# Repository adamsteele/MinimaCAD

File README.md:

Minima CAD
==========

Credit goes to Adrian over at http://yo4hhp.wordpress.com/ who did the original Eagle work and Ashhar Farhan over at http://www.phonestack.com/farhan/minima.html for the original Minima design.

There is a mailing list at http://www.freelists.org/archive/minima/recent for the Minima radio.

==========

What I've done is combine the two radio boards in to a single eagle brd/sch file and wrote up a BOM for DigiKey.
What I'd like to do is be able to run boards off at OSHPark, buy a bag of parts of DigiKey and have a radio.

What still needs done:

- [ ] Hole Drill Sizes. Adrian designed this for ease of home manufacture not for OSHPark so it will take some tweaks.
- [ ] Cleanup silkscreen. It's pretty clean already there's just a bit of overlap here and there.
- [ ] Cleanup part values for consistency
- [ ] Cleanup BOM. There are a few resistor/capacitor lines that could be combined.
- [ ] Verify BOM. I went through and generally picked the cheapest parts available. Many of these have fairly loose tolerances which might not work in a radio (I don't know).

==========

Quick Notes:
- These boards aren't ready yet for OSHPark so don't spend the money on it just yet.
- The BOM is reasonably complete but it is missing tuning inductors and a knob. Money could easily be saved by not buying SMA connectors and using a bit of coax. The LCD could also be bought elsewhere to save money.

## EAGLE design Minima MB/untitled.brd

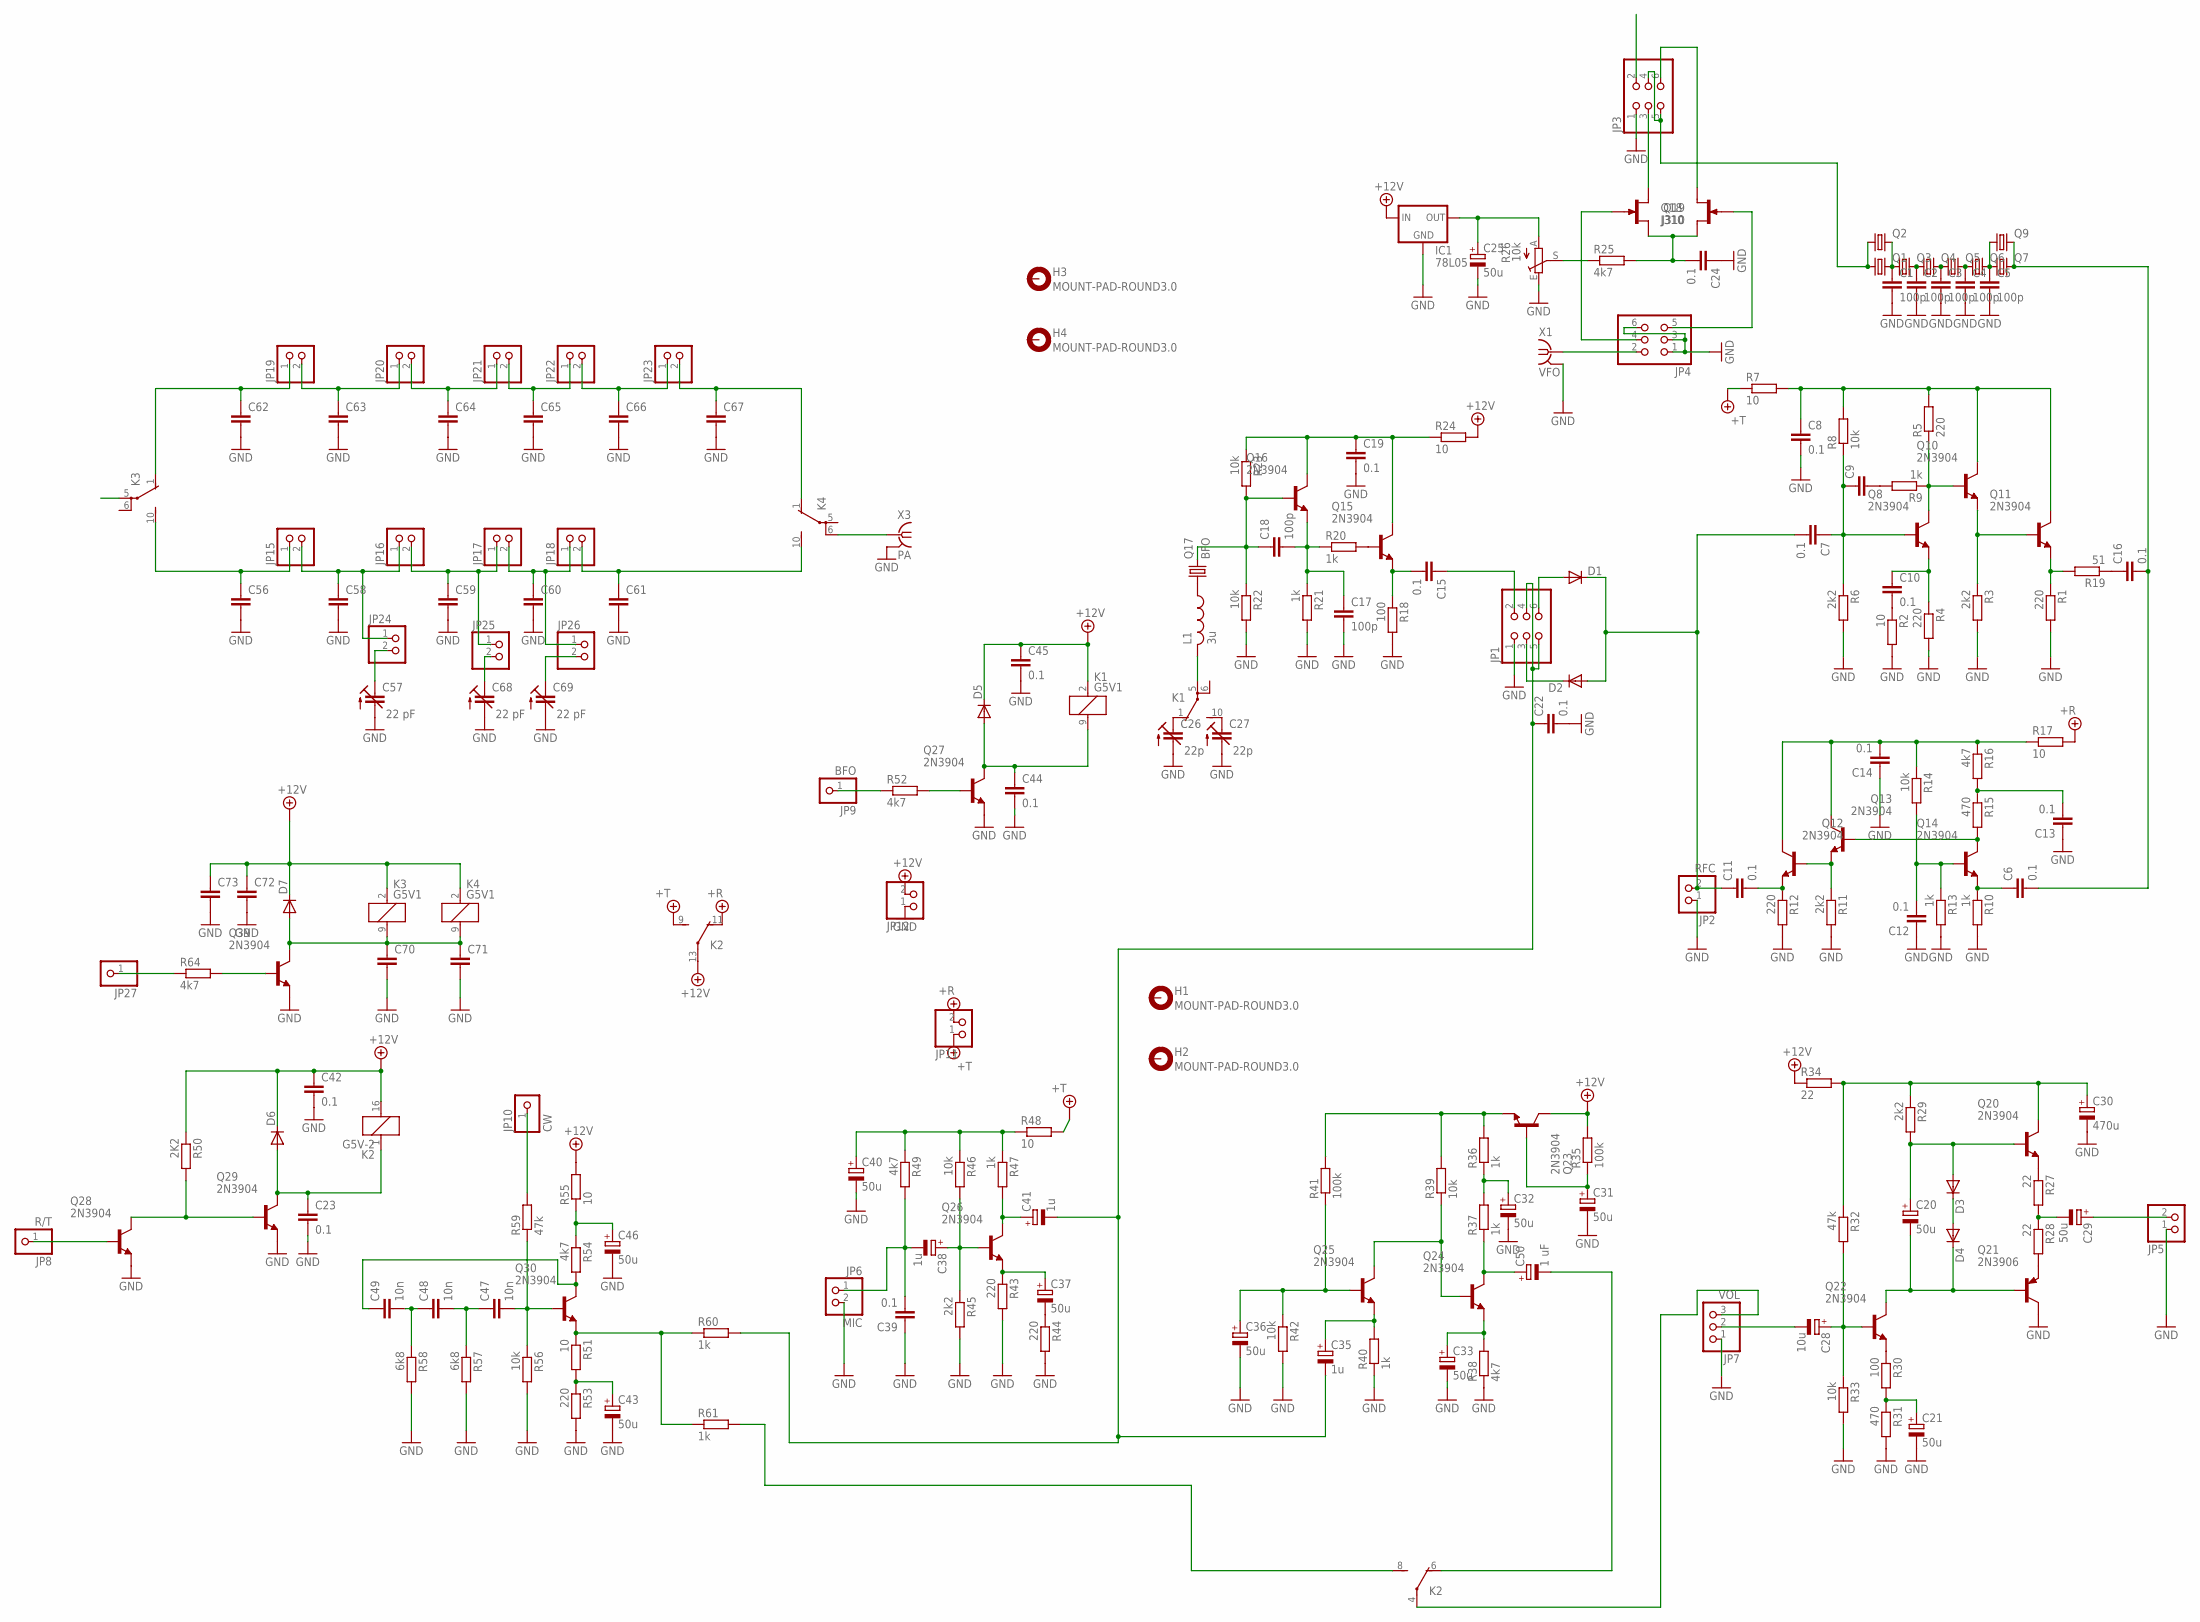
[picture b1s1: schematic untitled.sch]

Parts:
C1, C2, C3, C4, C5: 100p; C1206
C6, C7, C8, C10, C11, C12, C13, C14, C15, C16, C19, C22, C23, C24, C39, C42, C44, C45: 0.1; C050-024X044
C9, C56, C58, C59, C60, C61, C62, C63, C64, C65, C66, C67, C70, C71, C72, C73: C-EU050-024X044; C050-024X044
C17, C18: 100p; C050-024X044
C20, C21, C25, C29, C31, C32, C33, C36, C37, C40, C43, C46: 50u; E2,5-5
C26, C27: 22p; CTRIMTZ03
C28: 10u; E2,5-5
C30: 470u; E2,5-5
C35, C38, C41: 1u; E2,5-5
C47, C48, C49: 10n; C050-024X044
C50: 1 uF; E5-4
C57, C68, C69: 22 pF; CTRIMTZ03
D1, D2, D3, D4, D5, D6, D7: DIODE-D-5; D-5
H1, H2, H3, H4: MOUNT-PAD-ROUND3.0; 3,0-PAD
IC1: 78L05; 78LXX
JP1, JP3, JP4: PINHD-2X3; 2X03
JP2: RFC; 1X02
JP5, JP11, JP12, JP15, JP16, JP17, JP18, JP19, JP20, JP21, JP22, JP23, JP24, JP25, JP26: PINHD-1X2; 1X02
JP6: MIC; 1X02
JP7: VOL; 1X03
JP8: R/T; 1X01
JP9: BFO; 1X01
JP10: CW; 1X01
JP27: PINHD-1X1; 1X01
K1, K3, K4: G5V1
K2: G5V-2
L1: 3u; 0207/2V
Q1, Q2, Q3, Q4, Q5, Q6, Q7, Q9: CRYSTALHC49S; HC49/S
Q8, Q10, Q11, Q12, Q13, Q14, Q15, Q16, Q20, Q22, Q23, Q24, Q25, Q26, Q27, Q28, Q29, Q30, Q39: 2N3904; TO92
Q17: BFO; HC49/S
Q18, Q19: J310; TO92R
Q21: 2N3906; TO92
R1, R4, R5, R12, R43, R44, R53: 220; 0204/5
R2, R7, R17, R24, R48, R51, R55: 10; 0204/5
R3, R6, R11, R29, R45: 2k2; 0204/5
R8, R14, R22, R23, R33, R39, R42, R46, R56: 10k; 0204/5
R9, R10, R13, R20, R21, R36, R37, R40, R47, R60, R61: 1k; 0204/5
R15, R31: 470; 0204/5
R16, R25, R38, R49, R52, R54, R64: 4k7; 0204/5
R18, R30: 100; 0204/5
R19: 51; 0204/5
R26: 10k; CA6V
R27, R28, R34: 22; 0204/5
R32, R59: 47k; 0204/5
R35, R41: 100k; 0204/5
R50: 2K2; 0204/5
R57, R58: 6k8; 0204/5
X1: VFO; BU-SMA-V
X3: PA; BU-SMA-V

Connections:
+5V/1: JP11.2, K2.11 (O), R17.2
+5V/2: JP11.1, K2.9 (S), R7.1, R48.2
+12V: C42.1, C45.1, C72.1, C73.1, D5.C, D6.C, D7.C, IC1.IN, JP12.2, K1.2 (1), K2.13, K2.16 (2), K3.2 (1), K4.2 (1), Q23.1 (C), R24.2, R34.1, R35.2, R50.1, R55.2
GND: C1.2, C2.2, C3.2, C4.2, C5.2, C8.2, C12.1, C13.1, C14.1, C17.2, C19.2, C21.-, C22.2, C23.2, C24.1, C25.-, C26.2 (A), C27.2 (A), C30.-, C31.-, C32.-, C33.-, C36.-, C39.1, C40.-, C42.2, C43.-, C44.2, C45.2, C46.-, C56.2, C57.2 (A), C58.2, C59.2, C60.2, C61.2, C62.2, C63.2, C64.2, C65.2, C66.2, C67.2, C68.2 (A), C69.2 (A), C70.2, C71.2, C72.2, C73.2, IC1.GND, JP1.1, JP2.1, JP3.1, JP4.1, JP4.3, JP4.6, JP5.1, JP6.2, JP7.1, JP12.1, Q21.1 (C), Q27.3 (E), Q28.3 (E), Q29.3 (E), Q39.3 (E), R1.2, R2.2, R3.2, R4.2, R6.2, R10.2, R11.2, R12.2, R13.2, R18.2, R21.2, R22.2, R26.E, R31.2, R33.2, R38.1, R40.1, R42.2, R43.2, R44.2, R45.2, R53.2, R56.2, R57.2, R58.2, X1.2 (GND), X1.3 (GND), X1.4 (GND), X1.5 (GND), X3.2 (GND), X3.3 (GND), X3.4 (GND), X3.5 (GND)
unnamed: C1.1, Q1.2, Q2.2, Q3.1
unnamed: C2.1, Q3.2, Q4.1
unnamed: C3.1, Q4.2, Q5.1
unnamed: C4.1, Q5.2, Q6.1
unnamed: C5.1, Q6.2, Q7.1, Q9.1
unnamed: C6.2, C16.2, Q7.2, Q9.2
unnamed: C26.1 (E), K1.1 (O)
unnamed: C10.1, Q8.3 (E), R4.1
unnamed: C10.2, R2.1
unnamed: C7.1, C9.1, Q8.2 (B), R6.1, R8.1
unnamed: Q8.1 (C), Q10.2 (B), R5.1, R9.1
unnamed: Q10.3 (E), Q11.2 (B), R3.1
unnamed: Q11.3 (E), R1.1, R19.2
unnamed: C8.1, Q10.1 (C), Q11.1 (C), R5.2, R7.2, R8.2
unnamed: C16.1, R19.1
unnamed: C9.2, R9.2
unnamed: Q12.2 (B), Q13.3 (E), R11.1
unnamed: C11.2, Q12.3 (E), R12.1
unnamed: C14.2, Q12.1 (C), Q13.1 (C), R14.1, R16.1, R17.1
unnamed: C27.1 (E), K1.10 (S)
unnamed: C12.2, Q14.2 (B), R13.1, R14.2
unnamed: C6.1, Q14.3 (E), R10.1
unnamed: Q13.2 (B), Q14.1 (C), R15.2
unnamed: C13.2, R15.1, R16.2
unnamed: C15.2, Q15.3 (E), R18.1
unnamed: Q15.2 (B), R20.2
unnamed: C17.1, C18.2, Q16.3 (E), R20.1, R21.1
unnamed: C19.1, Q15.1 (C), Q16.1 (C), R23.1, R24.1
unnamed: C15.1, JP1.2
unnamed: C18.1, Q16.2 (B), Q17.2, R22.1, R23.2
unnamed: L1.1, Q17.1
unnamed: K1.5, L1.2
unnamed: R25.1, R26.S
unnamed: Q20.3 (E), R27.1
unnamed: Q27.2 (B), R52.2
unnamed: D1.A, JP1.6
unnamed: D2.C, JP1.3
unnamed: C7.2, C11.1, D1.C, D2.A, JP2.2
unnamed: JP3.4, JP3.5, Q1.1, Q2.1
unnamed: JP3.3, Q18.D
unnamed: JP3.6, Q19.D
unnamed: C24.2, Q18.S, Q19.S, R25.2
unnamed: JP4.5, Q19.G
unnamed: JP4.4, Q18.G
unnamed: C29.-, R27.2, R28.1
unnamed: JP4.2, X1.1
unnamed: Q21.3 (E), R28.2
unnamed: C25.+, IC1.OUT, R26.A
unnamed: D3.C, D4.A
unnamed: C20.-, D4.C, Q21.2 (B), Q22.1 (C)
unnamed: C20.+, D3.A, Q20.2 (B), R29.2
unnamed: C30.+, Q20.1 (C), R29.1, R32.1, R34.2
unnamed: Q22.3 (E), R30.1
unnamed: C21.+, R30.2, R31.1
unnamed: C28.+, Q22.2 (B), R32.2, R33.1
unnamed: C29.+, JP5.2
unnamed: C28.-, JP7.2
unnamed: C31.+, Q23.2 (B), R35.1
unnamed: Q23.3 (E), R36.2, R39.2, R41.2
unnamed: C32.+, R36.1, R37.2
unnamed: C50.+, Q24.1 (C), R37.1
unnamed: C33.+, Q24.3 (E), R38.2
unnamed: Q24.2 (B), Q25.1 (C), R39.1
unnamed: JP9.1, R52.1
unnamed: C35.+, Q25.3 (E), R40.2
unnamed: C36.+, Q25.2 (B), R41.1, R42.1
unnamed: C37.+, Q26.3 (E), R43.1
unnamed: C37.-, R44.1
unnamed: C38.+, Q26.2 (B), R45.1, R46.2
unnamed: C41.+, Q26.1 (C), R47.2
unnamed: C40.+, R46.1, R47.1, R48.1, R49.1
unnamed: C38.-, C39.2, JP6.1, R49.2
unnamed: JP7.3, K2.4
unnamed: C22.1, C35.-, C41.-, JP1.4, JP1.5, R60.2
unnamed: C50.-, K2.6 (O)
unnamed: JP8.1, Q28.2 (B)
unnamed: C23.1, D6.A, K2.1, Q29.1 (C)
unnamed: Q28.1 (C), Q29.2 (B), R50.2
unnamed: C44.1, D5.A, K1.9 (2), Q27.1 (C)
unnamed: Q30.3 (E), R51.1, R60.1, R61.1
unnamed: C43.+, R51.2, R53.1
unnamed: C49.1, Q30.1 (C), R54.2
unnamed: C46.+, R54.1, R55.1
unnamed: C47.2, Q30.2 (B), R56.1, R59.1
unnamed: C47.1, C48.2, R57.1
unnamed: C48.1, C49.2, R58.1
unnamed: JP10.1, R59.2
unnamed: K2.8 (S), R61.2
unnamed: C56.1, JP15.1, K3.10 (S)
unnamed: C58.1, JP15.2, JP16.1, JP24.1
unnamed: C59.1, JP16.2, JP17.1, JP25.1
unnamed: C60.1, JP17.2, JP18.1, JP26.1
unnamed: C61.1, JP18.2, K4.10 (S)
unnamed: C62.1, JP19.1, K3.1 (O)
unnamed: C63.1, JP19.2, JP20.1
unnamed: C64.1, JP20.2, JP21.1
unnamed: C65.1, JP21.2, JP22.1
unnamed: C66.1, JP22.2, JP23.1
unnamed: C67.1, JP23.2, K4.1 (O)
unnamed: K4.6, X3.1
unnamed: JP3.2, K3.5
unnamed: C57.1 (E), JP24.2
unnamed: C68.1 (E), JP25.2
unnamed: C69.1 (E), JP26.2
unnamed: Q39.2 (B), R64.2
unnamed: JP27.1, R64.1
unnamed: C70.1, C71.1, D7.A, K3.9 (2), K4.9 (2), Q39.1 (C)

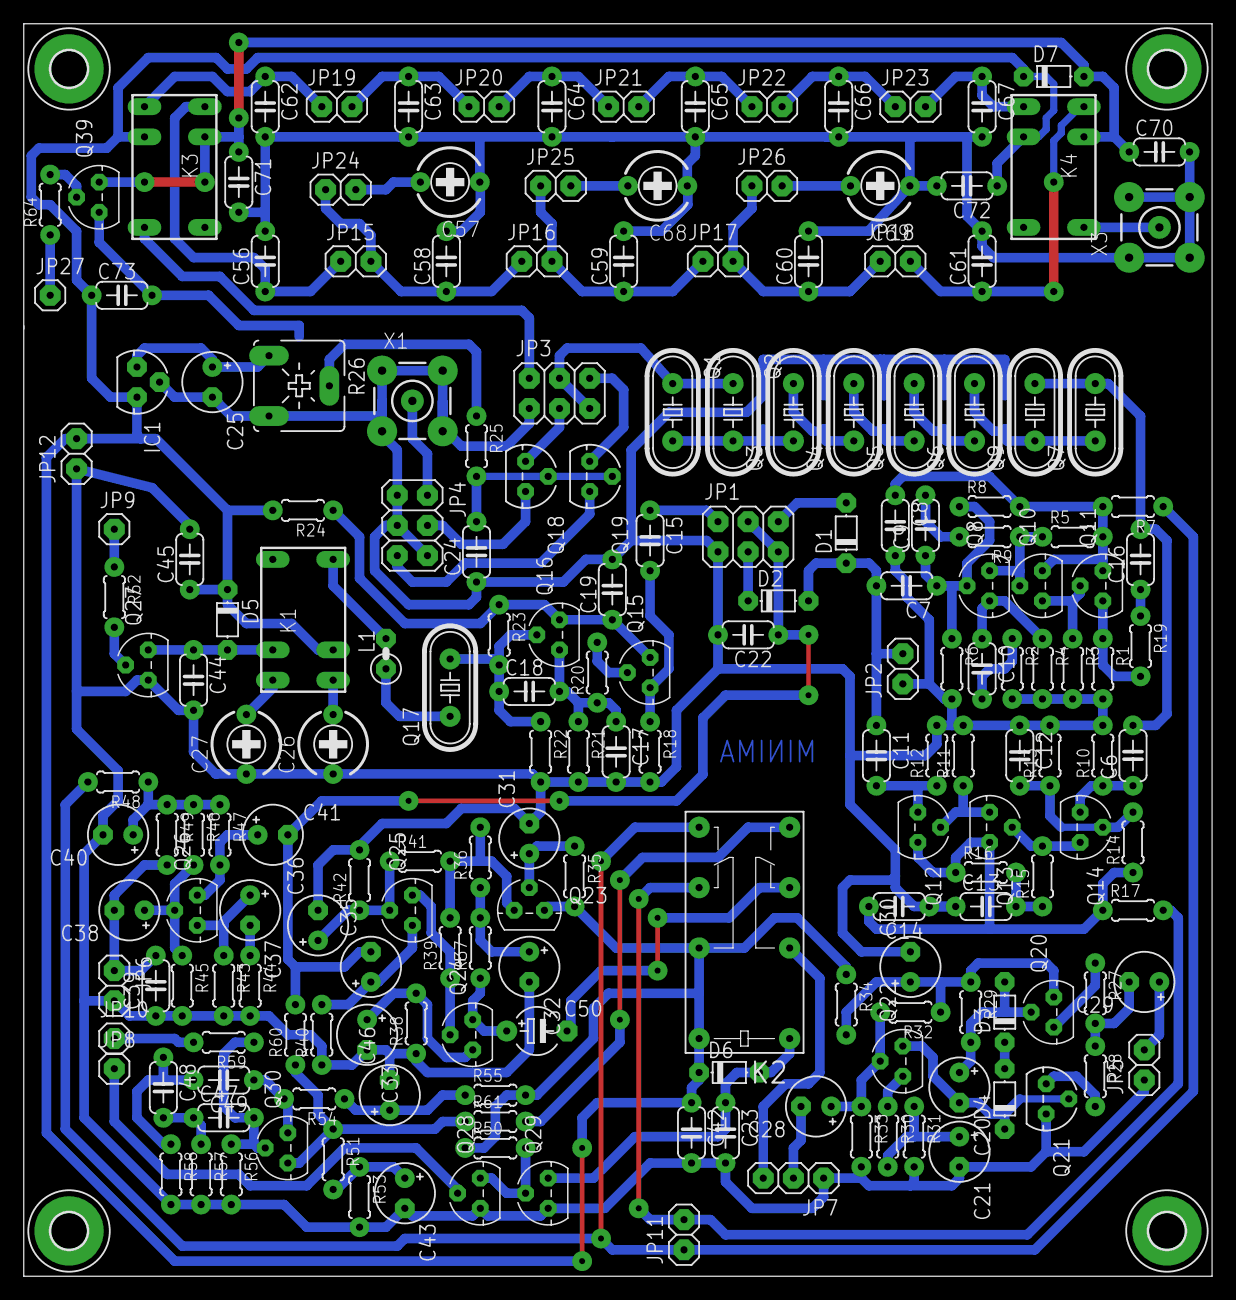
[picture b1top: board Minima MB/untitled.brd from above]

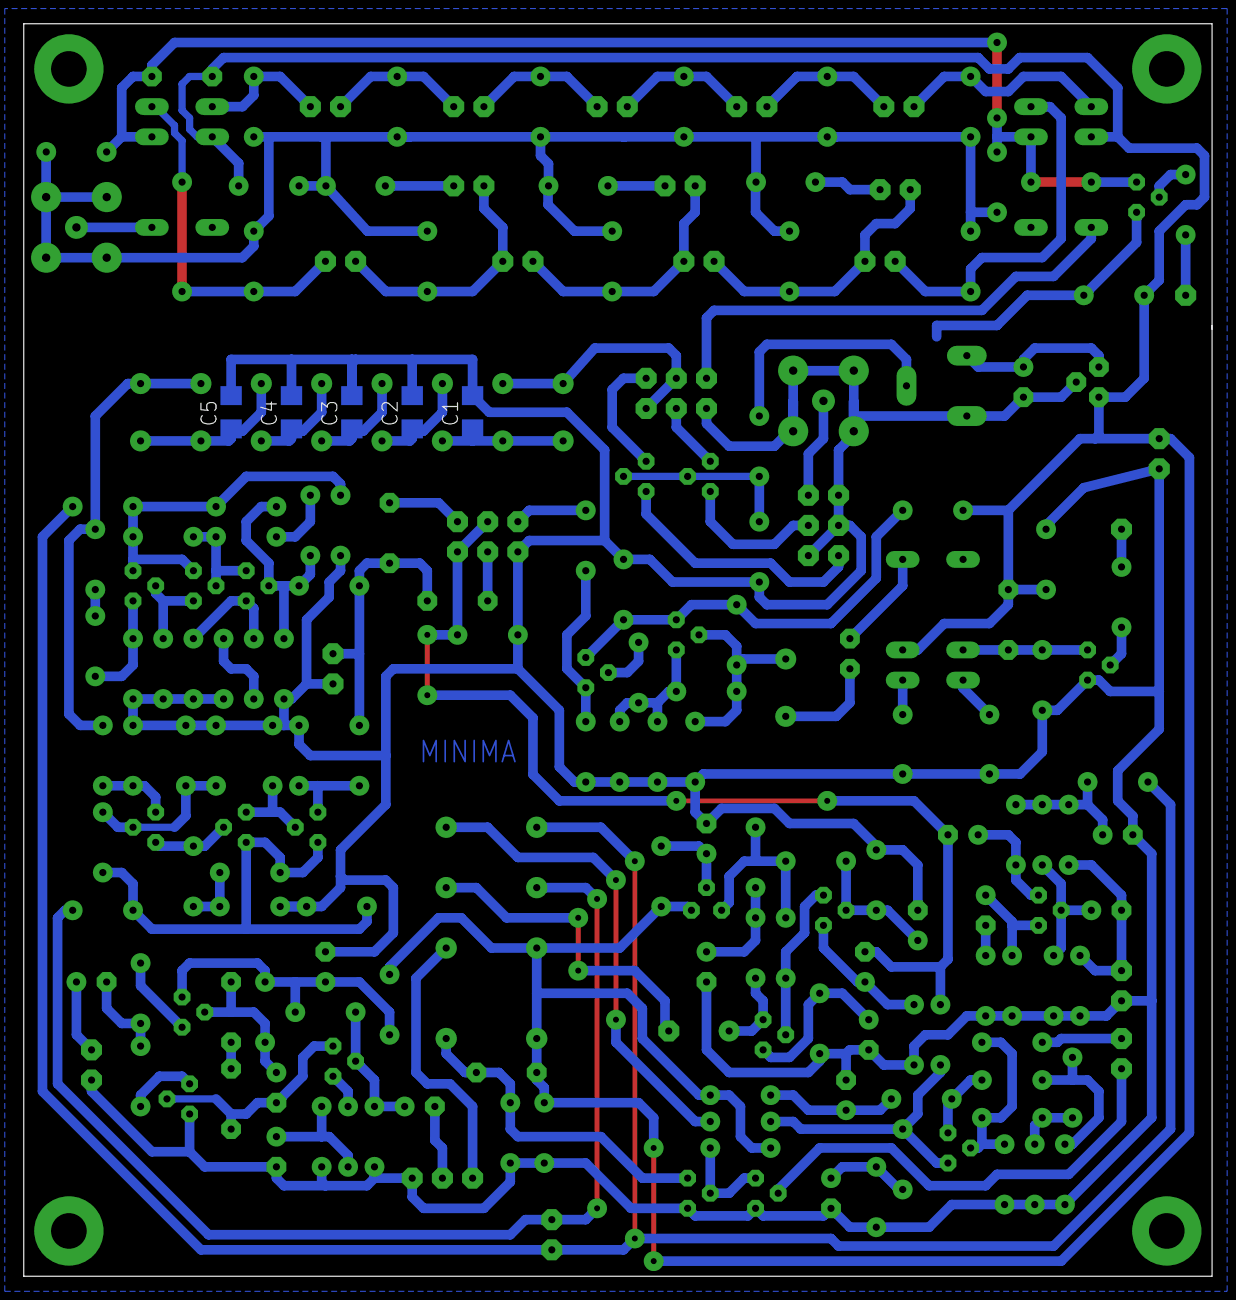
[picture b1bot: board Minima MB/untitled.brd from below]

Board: 2 copper layers, 100.0 x 105.4 mm, 204 parts (5 on the bottom side), 111 nets.

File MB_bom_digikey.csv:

Total part count:,,204,,,,BOM Cost:,$51.26,,
,,,,,,,,,
QTY,Value,Device,Parts,Description,Digikey P/N,Price at QTY,Total $,URL,
16,0.1 uF,C-EU050-024X044,"C9, C56, C58, C59, C60, C61, C62, C63,C64, C65, C66, C67, C70, C71, C72, C73","CAPACITOR, European symbol",445-8421-ND,$0.20,$3.20,http://www.digikey.com/product-detail/en/FK18X7R1E104K/445-8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,
3,22 pF,C-TRIMMTZ03,"C57, C68, C69",Trimm capacitor,SG3009-ND,$1.84,$5.52,http://www.digikey.com/product-detail/en/GYC65000/SG3009-ND/65256,
1,1 uF,CPOL-EUE5-4,C50,"POLARIZED CAPACITOR, European symbol",493-12600-1-ND,$0.15,$0.15,http://www.digikey.com/product-detail/en/UVK2A010MDD1TD/493-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,
8,20 MHz,CRYSTALHC49S,"Q1, Q2, Q3, Q4, Q5, Q6, Q7, Q9",CRYSTAL,CTX1106-ND,$0.36,$2.88,http://www.digikey.com/product-detail/en/ATS20A/CTX1106-ND/2640038,
3,1N4007,,"D1, D2, D3",DIODE,1N4007-TPMSCT-ND,$0.11,$0.33,http://www.digikey.com/product-detail/en/1N4007-TP/1N4007-TP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,
4,1N4148,DIODE-D-5,"D4, D5, D6, D7",DIODE,1N4148TACT-ND,$0.10,$0.40,http://www.digikey.com/product-detail/en/1N4148TA/1N4148TACT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,
1,-,PINHD-1X1,JP27,PIN HEADER,-,-,-,,
15,-,PINHD-1X2,"JP5, JP11, JP12, JP15, JP16, JP17, JP18, JP19, JP20, JP21, JP22, JP23, JP24, JP25, JP26",PIN HEADER,-,-,-,,
3,-,PINHD-2X3,"JP1, JP3, JP4",PIN HEADER,-,-,-,,
1,10k,R-EU_0204/5,R14,"RESISTOR, European symbol",CF18JT10K0CT-ND,$0.09,$0.09,http://www.digikey.com/product-detail/en/CF18JT10K0/CF18JT10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,
18,0.1,C-EU050-024X044,"C6, C7, C8, C10, C11, C12, C13, C14, C15, C16, C19, C22, C23, C24, C39, C42, C44, C45","CAPACITOR, European symbol",445-8421-ND,$0.20,$3.60,http://www.digikey.com/product-detail/en/FK18X7R1E104K/445-8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,
6,10,R-EU_0204/5,"R2, R7, R17, R24, R51, R55","RESISTOR, European symbol",CF18JT10R0CT-ND,$0.07,$0.39,http://www.digikey.com/product-detail/en/CF18JT10R0/CF18JT10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,
2,100,R-EU_0204/5,"R18, R30","RESISTOR, European symbol",CF18JT100RCT-ND,$0.09,$0.18,http://www.digikey.com/product-detail/en/CF18JT100R/CF18JT10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,
2,100k,R-EU_0204/5,"R35, R41","RESISTOR, European symbol",CF18JT100KCT-ND,$0.09,$0.18,http://www.digikey.com/product-detail/en/CF18JT100K/CF18JT10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,
2,100p,C-EU050-024X044,"C17, C18","CAPACITOR, European symbol",478-4214-1-ND,$0.25,$0.50,http://www.digikey.com/product-detail/en/5MQ101KOAAM/478-421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,
5,100p,C-EUC1206,"C1, C2, C3, C4, C5","CAPACITOR, European symbol",1276-2799-1-ND,$0.12,$0.60,http://www.digikey.com/product-detail/en/CL31C101JCCNFNC/127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,
8,10k,R-EU_0204/5,"R8, R22, R23, R33, R39, R42, R46, R56","RESISTOR, European symbol",CF18JT10K0CT-ND,$0.09,$0.72,http://www.digikey.com/product-detail/en/CF18JT10K0/CF18JT10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,
1,10k,TRIM_EU-CA6V,R26,POTENTIOMETER,3306F-103-ND,$0.41,$0.41,http://www.digikey.com/product-detail/en/3306F-1-103/3306F-1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,
3,10n,C-EU050-024X044,"C47, C48, C49","CAPACITOR, European symbol",445-8421-ND,$0.20,$0.60,http://www.digikey.com/product-detail/en/FK18X7R1E104K/445-8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,
1,10u,CPOL-EUE2.5-5,C28,"POLARIZED CAPACITOR, European symbol",493-12772-1-ND,$0.12,$0.12,http://www.digikey.com/product-detail/en/UVR1E100MDD6TP/493-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,
1,10,R-EU_0204/5,R48,"RESISTOR, European symbol",CF18JT10R0CT-ND,$0.07,$0.07,http://www.digikey.com/product-detail/en/CF18JT10R0/CF18JT10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,
11,1k,R-EU_0204/5,"R9, R10, R13, R20, R21, R36, R37, R40, R47, R60, R61","RESISTOR, European symbol",CF18JT1K00CT-ND,$0.07,$0.72,http://www.digikey.com/product-detail/en/CF18JT1K00/CF18JT1K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,
3,1u,CPOL-EUE2.5-5,"C35, C38, C41","POLARIZED CAPACITOR, European symbol",493-12600-1-ND,$0.15,$0.45,http://www.digikey.com/product-detail/en/UVK2A010MDD1TD/493-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,
3,22,R-EU_0204/5,"R27, R28, R34","RESISTOR, European symbol",CF18JT22R0CT-ND,$0.09,$0.27,http://www.digikey.com/product-detail/en/CF18JT22R0/CF18JT22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,
7,220,R-EU_0204/5,"R1, R4, R5, R12, R43, R44, R53","RESISTOR, European symbol",CF18JT220RCT-ND,$0.09,$0.63,http://www.digikey.com/product-detail/en/CF18JT220R/CF18JT22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,
2,22 pF,C-TRIMMTZ03,"C26, C27",Trimm capacitor,SG3009-ND,$1.84,$3.68,http://www.digikey.com/product-detail/en/GYC65000/SG3009-ND/65256,
1,2K2,R-EU_0204/5,R50,"RESISTOR, European symbol",CF18JT2K20CT-ND,$0.09,$0.09,http://www.digikey.com/product-detail/en/CF18JT2K20/CF18JT2K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,
19,2N3904,2N3904,"Q8, Q10, Q11, Q12, Q13, Q14, Q15, Q16, Q20, Q22, Q23, Q24, Q25, Q26, Q27, Q28, Q29, Q30, Q39",NPN Transistor,2N3904-APCT-ND,$0.17,$3.23,http://www.digikey.com/product-detail/en/2N3904-AP/2N3904-AP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,
1,2N3906,2N3906,Q21,PNP Transistor,2N3906-APCT-ND,$0.19,$0.19,http://www.digikey.com/product-detail/en/2N3906-AP/2N3906-AP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,
5,2k2,R-EU_0204/5,"R3, R6, R11, R29, R45","RESISTOR, European symbol",CF18JT2K20CT-ND,$0.09,$0.45,http://www.digikey.com/product-detail/en/CF18JT2K20/CF18JT2K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,
1,3u,L-US0207/2V,L1,"INDUCTOR, American symbol",495-5600-1-ND,$1.33,$1.33,http://www.digikey.com/product-detail/en/B82131A5202M/495-56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,
2,470,R-EU_0204/5,"R15, R31","RESISTOR, European symbol",CF18JT470RCT-ND,$0.09,$0.18,http://www.digikey.com/product-detail/en/CF18JT470R/CF18JT47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,
1,470u,CPOL-EUE2.5-5,C30,"POLARIZED CAPACITOR, European symbol",493-12892-1-ND,$0.18,$0.18,http://www.digikey.com/product-detail/en/UVY1A471MED1TD/493-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,
2,47k,R-EU_0204/5,"R32, R59","RESISTOR, European symbol",CF18JT47K0CT-ND,$0.09,$0.18,http://www.digikey.com/product-detail/en/CF18JT47K0/CF18JT47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,
7,4k7,R-EU_0204/5,"R16, R25, R38, R49, R52, R54, R64","RESISTOR, European symbol",CF18JT4K70CT-ND,$0.09,$0.63,http://www.digikey.com/product-detail/en/CF18JT4K70/CF18JT4K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,
12,50u,CPOL-EUE2.5-5,"C20, C21, C25, C29, C31, C32, C33, C36, C37, C40, C43, C46","POLARIZED CAPACITOR, European symbol",445-8425-ND,$0.22,$2.66,http://www.digikey.com/product-detail/en/FK18X7R1E474K/445-8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,
1,51,R-EU_0204/5,R19,"RESISTOR, European symbol",CF18JT51R0CT-ND,$0.09,$0.09,http://www.digikey.com/product-detail/en/CF18JT51R0/CF18JT51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,
2,6k8,R-EU_0204/5,"R57, R58","RESISTOR, European symbol",CF18JT6K80CT-ND,$0.09,$0.18,http://www.digikey.com/product-detail/en/CF18JT6K80/CF18JT6K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,
1,78L05,78LXX,IC1,VOLTAGE REGULATOR,497-2952-ND,$0.39,$0.39,http://www.digikey.com/product-detail/en/L78L05ACZ/497-2952-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,
1,20 MHz (BFO),CRYSTALHC49S,Q17,CRYSTAL,CTX1106-ND,$0.36,$0.36,http://www.digikey.com/product-detail/en/ATS20A/CTX1106-ND/2640038,
1,BFO,PINHD-1X1,JP9,PIN HEADER,-,-,-,,
1,CW,PINHD-1X1,JP10,PIN HEADER,-,-,-,,
1,12VDC,G5V-2,K2,OMRON PCB Relay,Z768-ND,$2.97,$2.97,http://www.digikey.com/product-detail/en/G5V-2-DC12/Z768-ND/87821,
3,G5V1,G5V1,"K1, K3, K4",RELAY,Z774-ND,$2.05,$6.15,http://www.digikey.com/product-detail/en/G5V-1-DC12/Z774-ND/87833,
2,J310,J310,"Q18, Q19","N-Channel RF Amplifier J309, J310",J310GOS-ND,$0.55,$1.10,http://www.digikey.com/product-detail/en/J310G/J310GOS-ND/918462,
1,MIC,PINHD-1X2,JP6,PIN HEADER,-,-,-,,
4,PAD-RND3.0,PAD-RND3.0,"H1, H2, H3, H4","MOUNTING PAD, round",-,-,-,,
1,PA,BU-SMA-V,X3,FEMALE SMA CONNECTOR,CONSMA001-ND,$2.61,$2.61,http://www.digikey.com/product-detail/en/CONSMA001/CONSMA001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,
1,R/T,PINHD-1X1,JP8,PIN HEADER,-,-,-,,
1,RFC,PINHD-1X2,JP2,PIN HEADER,-,-,-,,
1,VFO,BU-SMA-V,X1,FEMALE SMA CONNECTOR,CONSMA001-ND,$2.61,$2.61,http://www.digikey.com/product-detail/en/CONSMA001/CONSMA001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,
1,VOL,PINHD-1X3,JP7,PIN HEADER,-,-,-,,
,,,,,,,,,
,,,,,,,,,
,,,,,,,,,
,,,,,,,,,
,,,,,,,,,
,,,,,,,,,
,,,,,,,,,
,,,,,,,,,

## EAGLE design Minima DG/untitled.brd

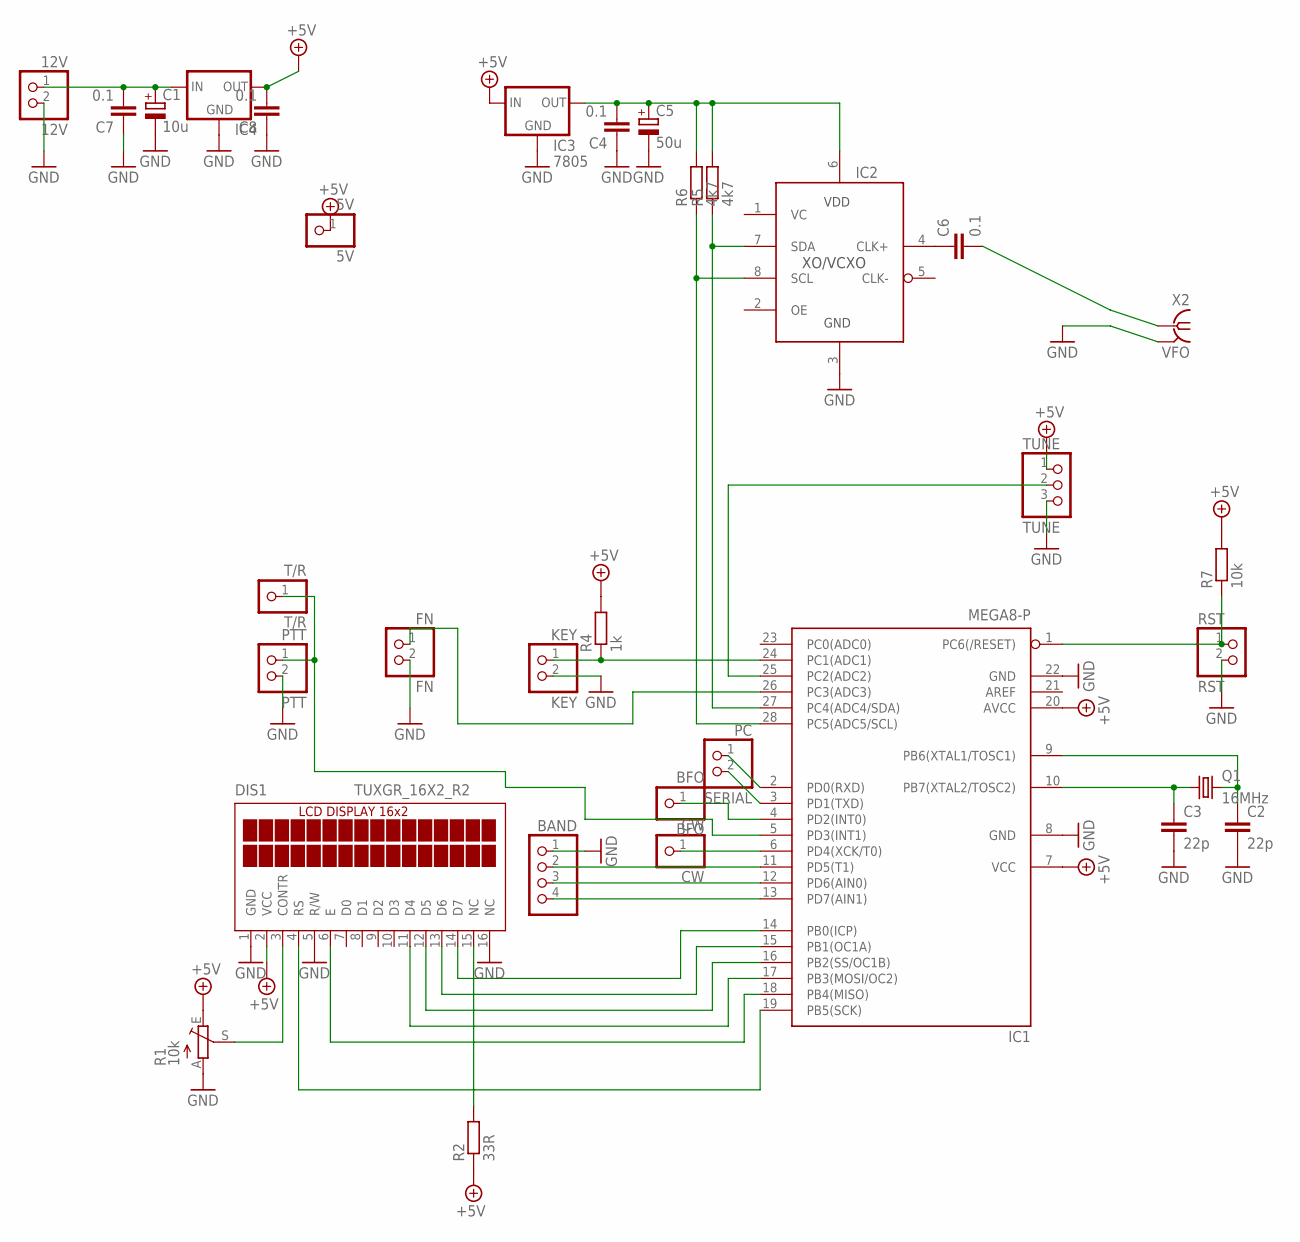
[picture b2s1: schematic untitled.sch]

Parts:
5V: 5V; 1X01
12V: 12V; 1X02
BAND: PINHD-1X4; 1X04
BFO: BFO; 1X01
C1: 10u; E2,5-5
C2, C3: 22p; C1206
C4, C6, C7, C8: 0.1; C050-024X044
C5: 50u; E2,5-5
CW: CW; 1X01
DIS1: TUXGR_16X2_R2
FN: FN; 1X02
IC1: MEGA8-P; DIL28-3
IC2: SI57X
IC3: 7805; TO252
IC4: 78XXL
KEY: KEY; 1X02
PC: SERIAL; 1X02
PTT: PTT; 1X02
Q1: 16MHz; HC49/S
R1: 10k; CA6V
R2: 33R; 0207/15
R4: 1k; 0204/5
R5, R6: 4k7; 0204/5
R7: 10k; 0204/5
RST: RST; 1X02
T/R: T/R; 1X01
TUNE: TUNE; 1X03
X2: VFO; BU-SMA-H

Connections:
+5V: 5V.1, C8.2, DIS1.2 (VCC), IC1.7 (VCC), IC1.20 (AVCC), IC3.2 (IN), IC4.OUT, R1.E, R2.1, R4.2, R7.2, TUNE.1
GND: 12V.2, BAND.1, C1.-, C2.2, C3.2, C4.1, C5.-, C7.1, C8.1, DIS1.1 (GND), DIS1.5 (R/W), DIS1.16 (NC), FN.2, IC1.8 (GND), IC1.22 (GND), IC2.3 (GND), IC3.1 (GND), IC4.GND, KEY.2, PTT.2, R1.A, RST.2, TUNE.3, X2.2 (GND), X2.3 (GND), X2.4 (GND), X2.5 (GND)
unnamed: DIS1.4 (RS), IC1.19 (PB5(SCK))
unnamed: DIS1.14 (D7), IC1.14 (PB0(ICP))
unnamed: DIS1.13 (D6), IC1.15 (PB1(OC1A))
unnamed: DIS1.12 (D5), IC1.16 (PB2(SS/OC1B))
unnamed: DIS1.11 (D4), IC1.17 (PB3(MOSI/OC2))
unnamed: DIS1.6 (E), IC1.18 (PB4(MISO))
unnamed: DIS1.3 (CONTR), R1.S
unnamed: DIS1.15 (NC), R2.2
unnamed: C2.1, IC1.9 (PB6(XTAL1/TOSC1)), Q1.2
unnamed: C3.1, IC1.10 (PB7(XTAL2/TOSC2)), Q1.1
unnamed: IC1.24 (PC1(ADC1)), KEY.1, R4.1
unnamed: BAND.2, IC1.11 (PD5(T1))
unnamed: BAND.3, IC1.12 (PD6(AIN0))
unnamed: BAND.4, IC1.13 (PD7(AIN1))
unnamed: FN.1, IC1.26 (PC3(ADC3))
unnamed: CW.1, IC1.6 (PD4(XCK/T0))
unnamed: IC1.5 (PD3(INT1)), PTT.1, T/R.1
unnamed: BFO.1, IC1.4 (PD2(INT0))
unnamed: IC1.27 (PC4(ADC4/SDA)), IC2.7 (SDA), R5.1
unnamed: IC1.28 (PC5(ADC5/SCL)), IC2.8 (SCL), R6.1
unnamed: C4.2, C5.+, IC2.6 (VDD), IC3.3 (OUT), R5.2, R6.2
unnamed: C6.1, IC2.4 (CLK+)
unnamed: C6.2, X2.1
unnamed: IC1.25 (PC2(ADC2)), TUNE.2
unnamed: IC1.1 (PC6(/RESET)), R7.1, RST.1
unnamed: 12V.1, C1.+, C7.2, IC4.IN
unnamed: IC1.2 (PD0(RXD)), PC.1
unnamed: IC1.3 (PD1(TXD)), PC.2

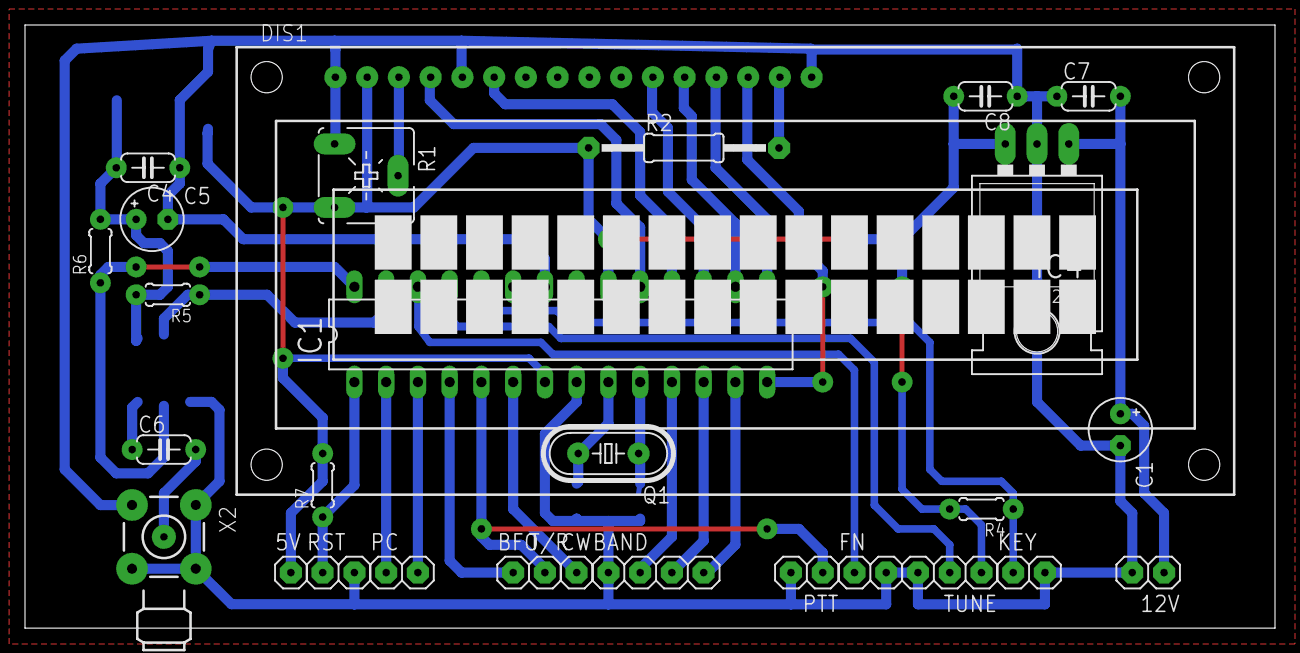
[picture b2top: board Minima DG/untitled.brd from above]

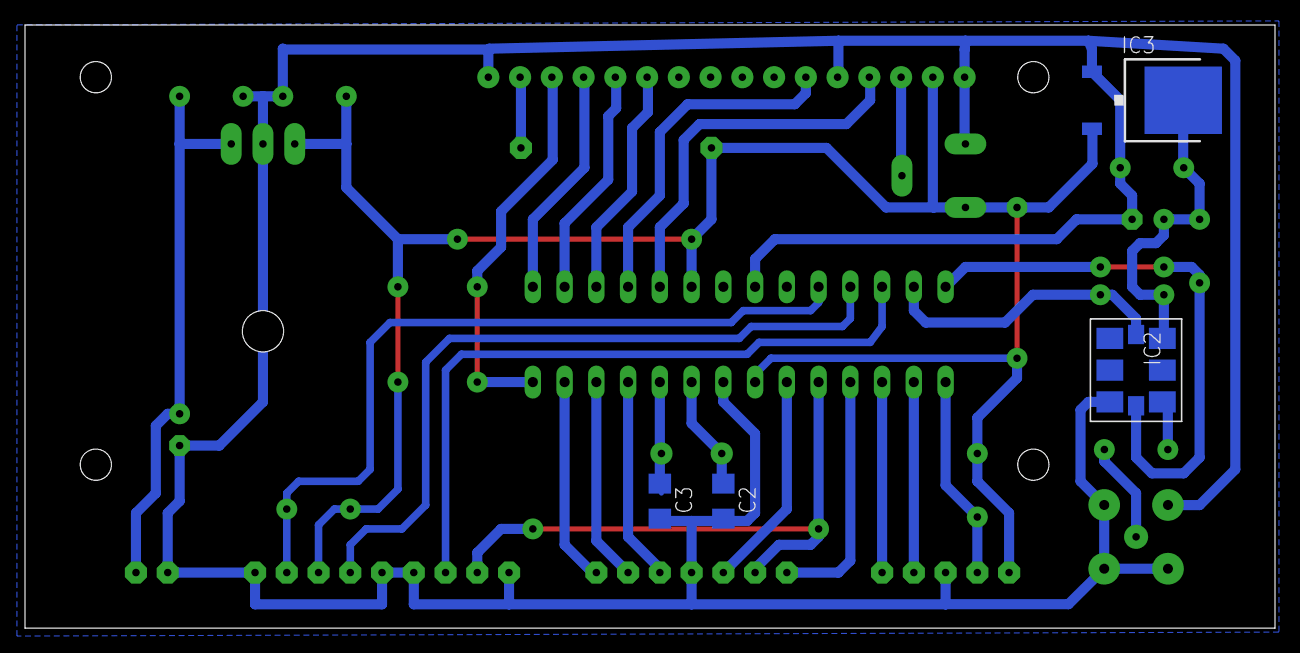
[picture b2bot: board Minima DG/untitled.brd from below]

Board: 2 copper layers, 100.0 x 48.2 mm, 33 parts (4 on the bottom side), 30 nets.

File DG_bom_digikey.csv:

Total part count:,,33,,,,BOM Cost:,$30.93,
,,,,,,,,
QTY,Value,Device,Parts,Description,Digikey P/N,Price at QTY,Total $,URL
1,,78XXL,IC4,VOLTAGE REGULATOR,MC7805CT-BPMS-ND,$0.48,$0.48,http://www.digikey.com/product-detail/en/MC7805CT-BP/MC7805C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
1,,PINHD-1X4,BAND,PIN HEADER,-,-,-,-
1,,SI57X,IC2,Any Rate I2C Prorammable XO/VCXO SiliconLabs Si570 XO and Si571 VCXO,336-2518-ND,$13.11,$13.11,http://www.digikey.com/product-detail/en/570CAC000141DG/336-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
4,0.1,C-EU050-024X044,"C4, C6, C7, C8","CAPACITOR, European symbol",445-8421-ND,$0.20,$0.80,http://www.digikey.com/product-detail/en/FK18X7R1E104K/445-8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
1,10k,R-EU_0204/5,R7,"RESISTOR, European symbol",CF18JT10K0CT-ND,$0.09,$0.09,http://www.digikey.com/product-detail/en/CF18JT10K0/CF18JT10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
1,10k,TRIM_EU-CA6V,R1,POTENTIOMETER,3306F-103-ND,$0.41,$0.41,http://www.digikey.com/product-detail/en/3306F-1-103/3306F-1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
1,10u,CPOL-EUE2.5-5,C1,"POLARIZED CAPACITOR, European symbol",493-12772-1-ND,$0.12,$0.12,http://www.digikey.com/product-detail/en/UVR1E100MDD6TP/493-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
1,12V,PINHD-1X2,12V,PIN HEADER,-,-,-,-
1,16MHz,CRYSTALHC49S,Q1,CRYSTAL,CTX1085-ND,$0.36,$0.36,http://www.digikey.com/product-detail/en/ATS16B/CTX1085-ND/2640031
1,1k,R-EU_0204/5,R4,"RESISTOR, European symbol",CF18JT1K00CT-ND,$0.07,$0.07,http://www.digikey.com/product-detail/en/CF18JT1K00/CF18JT1K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
2,22p,C-EUC1206,"C2, C3","CAPACITOR, European symbol",1276-2820-1-ND,$0.10,$0.20,http://www.digikey.com/product-detail/en/CL31C220JCCNNNC/127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
1,33R,R-EU_0207/15,R2,"RESISTOR, European symbol",CF14JT33R0CT-ND,$0.08,$0.08,http://www.digikey.com/product-detail/en/CF14JT33R0/CF14JT33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
2,4k7,R-EU_0204/5,"R5, R6","RESISTOR, European symbol",CF18JT4K70CT-ND,$0.09,$0.18,http://www.digikey.com/product-detail/en/CF18JT4K70/CF18JT4K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
1,50u,CPOL-EUE2.5-5,C5,"POLARIZED CAPACITOR, European symbol",493-12597-1-ND,$0.15,$0.15,http://www.digikey.com/product-detail/en/UVK1V470MDD1TD/493-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
1,5V,PINHD-1X1,5V,PIN HEADER,-,-,-,-
1,7805,LM1117TO252,IC3,,1016-1584-1-ND,$0.66,$0.66,http://www.digikey.com/product-detail/en/SP7805V2-L%2FTR/101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
1,BFO,PINHD-1X1,BFO,PIN HEADER,-,-,-,-
1,CW,PINHD-1X1,CW,PIN HEADER,-,-,-,-
1,FN,PINHD-1X2,FN,PIN HEADER,-,-,-,-
1,KEY,PINHD-1X2,KEY,PIN HEADER,-,-,-,-
1,MEGA8-P,MEGA8-P,IC1,MICROCONTROLLER,ATMEGA328P-PU-ND,$3.23,$3.23,http://www.digikey.com/product-detail/en/ATMEGA328P-PU/ATMEG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
1,PTT,PINHD-1X2,PTT,PIN HEADER,-,-,-,-
1,RST,PINHD-1X2,RST,PIN HEADER,-,-,-,-
1,SERIAL,PINHD-1X2,PC,PIN HEADER,-,-,-,-
1,T/R,PINHD-1X1,T/R,PIN HEADER,-,-,-,-
1,TUNE,PINHD-1X3,TUNE,PIN HEADER,-,-,-,-
1,TUXGR_16X2_R2,TUXGR_16X2_R2,DIS1,"Tuxgraphics LCD display 16x2 characters reflective, without background light",67-1781-ND,$8.38,$8.38,http://www.digikey.com/product-detail/en/LCM-S01602DTR%2FM/6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
1,VFO,BU-SMA-H,X2,FEMALE SMA CONNECTOR,CONSMA001-ND,$2.61,$2.61,http://www.digikey.com/product-detail/en/CONSMA001/CONSMA001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
,,,,,,,,
